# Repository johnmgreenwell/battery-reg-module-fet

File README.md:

# Battery Regulator Module (N-FET Version)

Custom lithium-polymer battery voltage monitor and regulator module (N-FET version).

## Overview

This custom module is designed as a drop-in for small-scale electronics projects providing 3.3V linear regulated voltage output from a raw lithium polymer cell input. The battery input voltage is monitored by the [MIC2779](https://www.digikey.com/en/products/detail/microchip-technology/MIC2779L-2YM5-TR/1616864) whose output enables or disables the regulated output supply. It is configured with hysteresis to cutoff output when the battery voltage reaches 3.1V and to then hold in reset until the battery voltage exceeds 3.6V.

This is a form-factor-compatible replacement for the battery regulator module design available [here](https://github.com/johnmgreenwell/battery-reg-module). This version makes use of an N-FET transistor for switching rather than the built-in enable used in the original design. This version is meant to serve as a alternate to be used on the basis of parts-available.

The module supports the 1.5A maximum current limitations of the regulator chip [AP7363](https://www.digikey.com/en/products/detail/diodes-incorporated/AP7363-33D-13/3829401) used.

This module may be combined with a Lipo charger module such as the [TP4056](https://www.best-microcontroller-projects.com/tp4056.html) (along with any in-circuit charging mods as required) for a complete custom battery charging/monitoring/regulation for small-scale electronics projects.

The zipped gerber files provided may be uploaded to a PCB manufacturer for fabrication. Below is the automatic rendering of the uploaded gerbers by [OSHPark](https://oshpark.com/home).

## Schematic

The schematic for the circuit is provided below as designed in Kicad 9.

## License

MIT © 2024 John Greenwell

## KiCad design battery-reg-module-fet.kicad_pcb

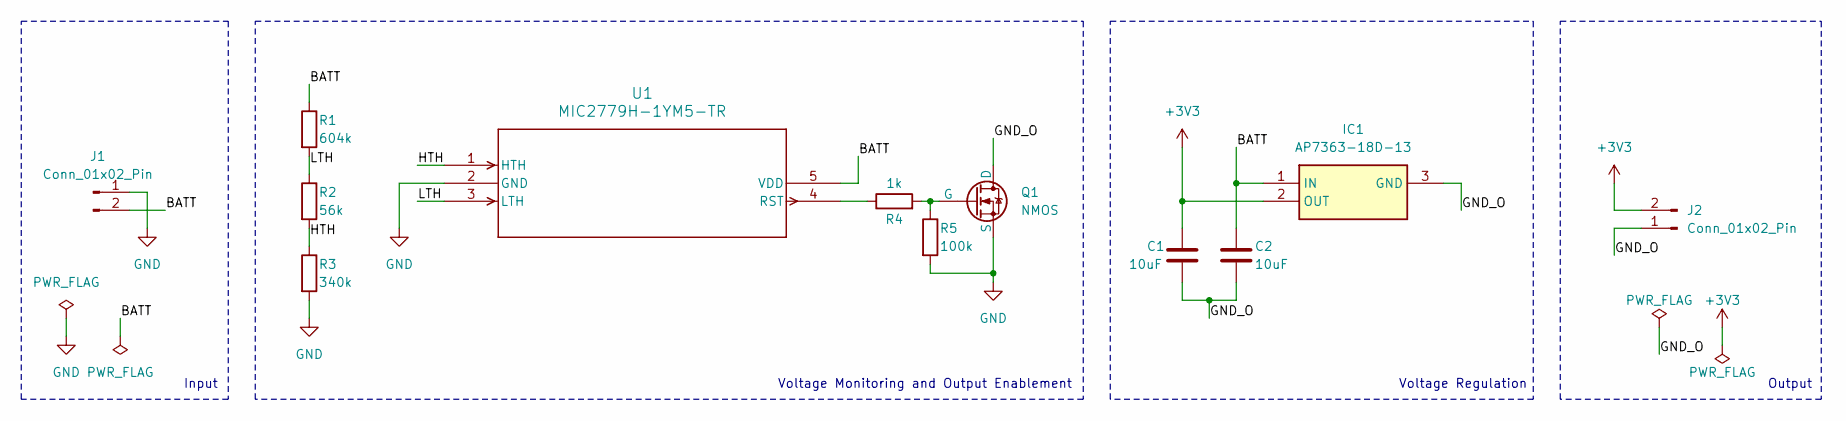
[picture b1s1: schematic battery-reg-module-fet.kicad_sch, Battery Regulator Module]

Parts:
C1, C2: 10uF; C_0603_1608Metric
IC1: AP7363-18D-13; TO252__DPAK__1; Manufacturer_Part_Number AP7363-18D-13; Mouser Part Number 621-AP7363-18D-13
J1, J2: Conn_01x02_Pin; PinHeader_1x02_P2.54mm_Vertical
Q1: NMOS; SOT-323_SC-70_Handsoldering
R1: 604k; R_0603_1608Metric_Pad0.98x0.95mm_HandSolder
R2: 56k; R_0603_1608Metric_Pad0.98x0.95mm_HandSolder
R3: 340k; R_0603_1608Metric_Pad0.98x0.95mm_HandSolder
R4: 1k; R_0603_1608Metric_Pad0.98x0.95mm_HandSolder
R5: 100k; R_0603_1608Metric_Pad0.98x0.95mm_HandSolder
U1: MIC2779H-1YM5-TR; SOT-23-5_M5_MCH-L

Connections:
+3V3: C1.1, IC1.2 (OUT), J2.2
/BATT: C2.1, IC1.1 (IN), J1.2, R1.1, U1.5 (VDD)
/GND_O: C1.2, C2.2, IC1.3 (GND), J2.1, Q1.1 (D)
/HTH: R2.2, R3.1, U1.1 (HTH)
/LTH: R1.2, R2.1, U1.3 (LTH)
GND: J1.1, Q1.3 (S), R3.2, R5.2, U1.2 (GND)
unnamed: Q1.2 (G), R4.2, R5.1
unnamed: R4.1, U1.4 (RST)

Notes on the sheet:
Voltage Regulation
Input
Output
Voltage Monitoring and Output Enablement

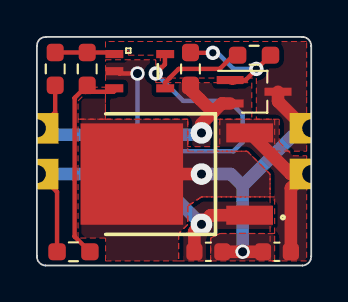
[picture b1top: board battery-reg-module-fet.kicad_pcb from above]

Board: 2 copper layers, 15.2 x 12.7 mm, 12 parts (0 on the bottom side), 8 nets.

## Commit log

2024-01-31 Add comparison repo link to readme
2024-02-14 Add gerbers, image of gerber rendering
2024-09-27 Update cad files for kicad 8
2025-04-13 Update cad files to kicad 9
2025-04-13 Update readme to reference kicad 9

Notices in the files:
battery-reg-module-fet.kicad_pcb:
© JMG 2024
battery-reg-module-fet.kicad_sch:
© John Greenwell 2024
